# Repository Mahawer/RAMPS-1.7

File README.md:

# RAMPS 1.7

This is an Improvment over the ancient RAMPS 1.4 and later RAMPS 1.5/1.6 made by BIGTREETECH.

Backwards compatible with RAMPS 1.4 in Marlin. All pin definetions are the same.

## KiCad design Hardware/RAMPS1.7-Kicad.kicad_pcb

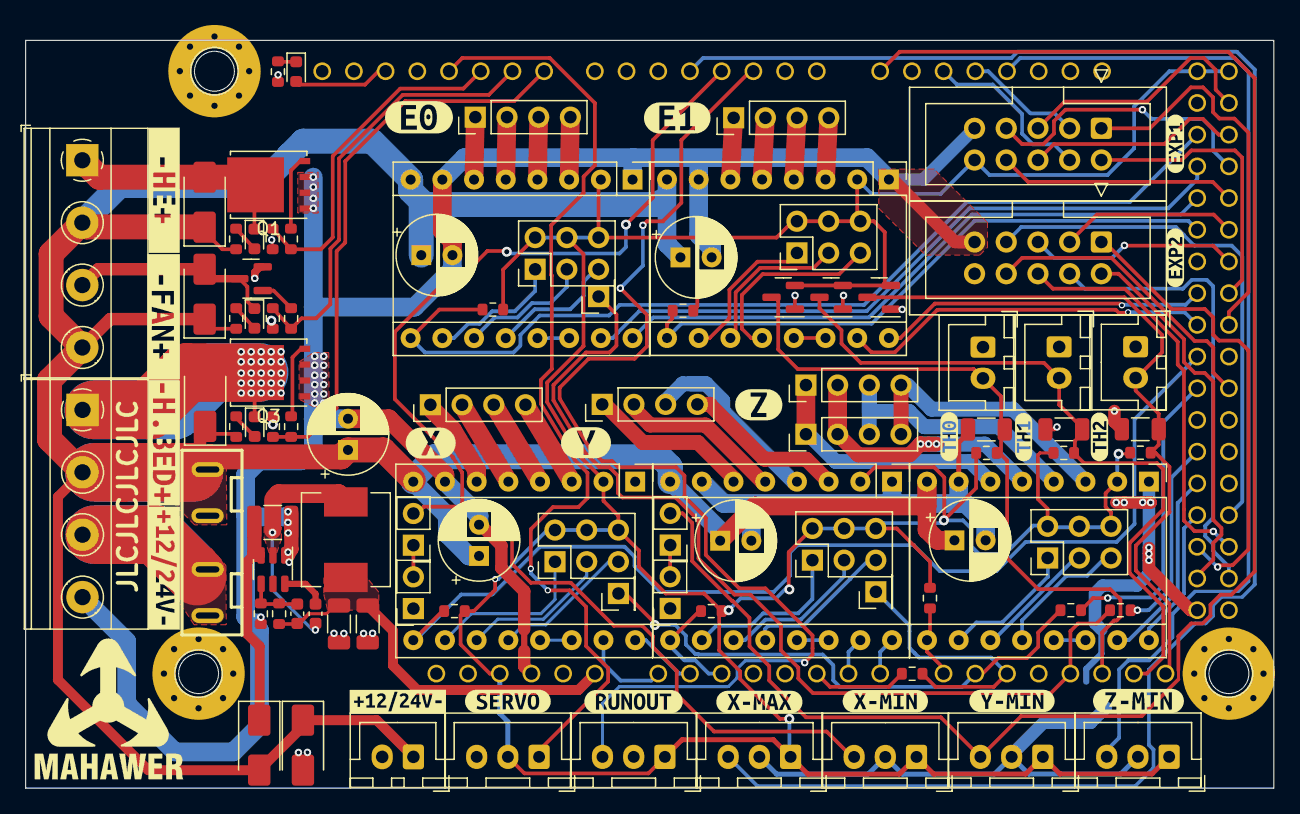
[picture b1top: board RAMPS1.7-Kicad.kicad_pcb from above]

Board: 2 copper layers, 100.0 x 59.9 mm, 117 parts (0 on the bottom side), 111 nets.

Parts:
A1, A2, A3, A4, A5: Pololu_Breakout_A4988; Pololu_Breakout-16_15.2x20.3mm
C1, C2, C3, C4, C5, C14: 100u; CP_Radial_D6.3mm_P2.50mm
C6, C7, C8: 10u; C_1206_3216Metric
C9: 100n; C_0603_1608Metric
C10: 10u; C_1210_3225Metric
C11: 68p; C_0603_1608Metric
C12, C13: 22u; C_1206_3216Metric
D1: LED_Small; LED_0603_1608Metric
D2, D3, D12: BAV99; SOT-23
D4, D5, D6, D8, D10: D; D_SMA
D7, D9, D11: LED; LED_0603_1608Metric
EXP1, EXP2: Conn_02x05_Odd_Even; IDC-Header_2x05_P2.54mm_Vertical
F1: Fuse; FUSE-TH_XF-506P
H1, H2, H3: MountingHole_Pad; MountingHole_3.7mm_Pad_Via
J1, J2: XD; PinSocket_1x02_P2.54mm_Vertical
J3, J4: XS; PinHeader_1x02_P2.54mm_Vertical
J5, J6, J7, J13, J14, J29: X; PinHeader_1x04_P2.54mm_Vertical
J8, J9, J10, J15, J16: Conn_02x03_Odd_Even; PinHeader_2x03_P2.54mm_Vertical
J11, J12, J17: Conn_01x01_Socket; PinHeader_1x01_P2.54mm_Vertical
J18, J30: X-STOP; JST_XH_B3B-XH-A_1x03_P2.50mm_Vertical
J19: Y-STOP; JST_XH_B3B-XH-A_1x03_P2.50mm_Vertical
J20: TH0; JST_XH_B2B-XH-A_1x02_P2.50mm_Vertical
J21: Z-STOP; JST_XH_B3B-XH-A_1x03_P2.50mm_Vertical
J22: TH1; JST_XH_B2B-XH-A_1x02_P2.50mm_Vertical
J23: E0-DET; JST_XH_B3B-XH-A_1x03_P2.50mm_Vertical
J24: E1-DET; JST_XH_B3B-XH-A_1x03_P2.50mm_Vertical
J25: THB; JST_XH_B2B-XH-A_1x02_P2.50mm_Vertical
J26, J28: HEATERS; TerminalBlock_Phoenix_MKDS-1,5-4_1x04_P5.00mm_Horizontal
J27: FAN2; JST_XH_B2B-XH-A_1x02_P2.50mm_Vertical
L1: 10u; L_Sunlord_MWSA0603S
Q1: HY1603; TDSON-8-1
Q2: AO3400A; SOT-23
Q3: HYG023N03; TDSON-8-1
R1, R2, R3, R4, R5: 10K; R_0603_1608Metric
R6, R7, R8, R12, R15, R18, R23: 4.7k; R_0603_1608Metric
R9, R11, R14, R17: 100k; R_0603_1608Metric
R10: 13.3k; R_0603_1608Metric
R13, R16, R19: 10r; R_0603_1608Metric
R20, R21, R22: 1K; R_0603_1608Metric
U1: ARDUINO_MEGA_SHIELD
U2: TPS54202; SOT-23-6
kibuzzard-643BE5C7: G***; kibuzzard-643BE5C7
kibuzzard-643BF197: G***; kibuzzard-643BF197
kibuzzard-643C2A90: G***; kibuzzard-643C2A90
kibuzzard-643C090C: G***; kibuzzard-643C090C
kibuzzard-646BE892: G***; kibuzzard-646BE892
kibuzzard-64628A92: G***; kibuzzard-64628A92
kibuzzard-64628CD2: G***; kibuzzard-64628CD2
kibuzzard-64628D02: G***; kibuzzard-64628D02
kibuzzard-646285C1: G***; kibuzzard-646285C1
kibuzzard-646285F2: G***; kibuzzard-646285F2
kibuzzard-646286CB: G***; kibuzzard-646286CB
kibuzzard-646288A1: G***; kibuzzard-646288A1
kibuzzard-646288B6: G***; kibuzzard-646288B6
kibuzzard-646288C0: G***; kibuzzard-646288C0
kibuzzard-646288CA: G***; kibuzzard-646288CA
kibuzzard-6462874F: G***; kibuzzard-6462874F
kibuzzard-6462890D: G***; kibuzzard-6462890D
kibuzzard-64628626: G***; kibuzzard-64628626
kibuzzard-64628682: G***; kibuzzard-64628682
kibuzzard-64628719: G***; kibuzzard-64628719
kibuzzard-64656097: G***; kibuzzard-64656097

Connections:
+5V: A1.2 (VDD), A2.2 (VDD), A3.2 (VDD), A4.2 (VDD), A5.2 (VDD), D2.2 (A), D3.2 (A), D12.2 (A), EXP1.10, J8.2, J8.4, J8.6, J9.2, J9.4, J9.6, J10.2, J10.4, J10.6, J15.2, J15.4, J15.6, J16.2, J16.4, J16.6, J18.1, J19.1, J21.1, J23.2, J24.1, J30.1, R1.1, R2.1, R3.1, R4.1, R5.1, R6.1, R7.1, R8.1, U1.5V@0, U1.5V@1, U1.5V@2
+24V: A1.8 (VMOT), A2.8 (VMOT), A3.8 (VMOT), A4.8 (VMOT), A5.8 (VMOT), C1.1, C2.1, C3.1, C4.1, C5.1, C14.1, D4.2 (A), D5.1 (K), D6.1 (K), D8.1 (K), D10.1 (K), F1.2, J26.2, J26.4, J27.1, J28.2, R12.2, R15.2, R18.2
A5: R21.2, U1.A5
A9: J11.1, R20.1, U1.A9
A10: J12.1, R21.1, U1.A10
A12: J17.1, R22.1, U1.A12
AM-VIN: C11.1, C12.1, C13.1, L1.2, R9.1, U1.VIN
D4: J24.3, U1.D4
D8: R17.2, R19.2, U1.D8
D9: R14.2, R16.2, U1.D9
D10: R11.2, R13.2, U1.D10
D11: J23.1, U1.D11
D16: EXP1.4, U1.D16
D17: EXP1.3, U1.D17
D23: EXP1.5, U1.D23
D25: EXP1.6, U1.D25
D27: EXP1.7, U1.D27
D29: EXP1.8, U1.D29
D31: EXP2.3, U1.D31
D33: EXP2.5, U1.D33
D35: EXP1.2, U1.D35
D37: EXP1.1, U1.D37
D40: R20.2, U1.D40
D41: EXP2.8, U1.D41
D44: R22.2, U1.D44
D49: EXP2.7, U1.D49
D53: EXP2.4, U1.D53
DCIN: F1.1, J28.3
E0_DIR: A4.16 (DIR), U1.D28
E0_EN: A4.9 (~ENABLE), R4.2, U1.D24
E0_STEP: A4.15 (STEP), U1.D26
E1_DIR: A5.16 (DIR), U1.D34
E1_EN: A5.9 (~ENABLE), R5.2, U1.D30
E1_STEP: A5.15 (STEP), U1.D36
GND: A1.1 (GND), A1.7 (GND), A2.1 (GND), A2.7 (GND), A3.1 (GND), A3.7 (GND), A4.1 (GND), A4.7 (GND), A5.1 (GND), A5.7 (GND), C1.2, C2.2, C3.2, C4.2, C5.2, C6.1, C7.1, C8.1, C10.2, C12.2, C13.2, C14.2, D2.1 (K), D3.1 (K), D5.2 (A), D12.1 (K), EXP1.9, EXP2.9, J18.2, J19.2, J20.1, J21.2, J22.1, J23.3, J24.2, J25.1, J27.2, J28.4, J30.2, Q1.1 (S), Q1.2 (S), Q1.3 (S), Q2.2 (S), Q3.1 (S), Q3.2 (S), Q3.3 (S), R10.2, R11.1, R14.1, R17.1, R23.2, U1.GND@0, U1.GND@1, U1.GND@2, U1.GND@3, U1.GND@4, U2.1 (GND)
LED: D1.2 (A), U1.D13
MISO: EXP2.1, U1.D50
MOSI: EXP2.6, U1.D51
unnamed: A1.4 (1A), J5.3
unnamed: A1.3 (1B), J5.4
unnamed: A1.5 (2A), J5.2
unnamed: A1.6 (2B), J5.1
unnamed: A1.10 (MS1), J8.1
unnamed: A1.11 (MS2), J8.3
unnamed: A1.12 (MS3), J8.5
unnamed: A1.13 (~RESET), A1.14 (~SLEEP)
unnamed: A2.4 (1A), J6.3
unnamed: A2.3 (1B), J6.4
unnamed: A2.5 (2A), J6.2
unnamed: A2.6 (2B), J6.1
unnamed: A2.10 (MS1), J9.1
unnamed: A2.11 (MS2), J9.3
unnamed: A2.12 (MS3), J9.5
unnamed: A2.13 (~RESET), A2.14 (~SLEEP)
unnamed: A3.4 (1A), J7.3, J29.3
unnamed: A3.3 (1B), J7.4, J29.4
unnamed: A3.5 (2A), J7.2, J29.2
unnamed: A3.6 (2B), J7.1, J29.1
unnamed: A3.10 (MS1), J10.1
unnamed: A3.11 (MS2), J10.3
unnamed: A3.12 (MS3), J10.5
unnamed: A3.13 (~RESET), A3.14 (~SLEEP)
unnamed: A4.4 (1A), J13.3
unnamed: A4.3 (1B), J13.4
unnamed: A4.5 (2A), J13.2
unnamed: A4.6 (2B), J13.1
unnamed: A4.10 (MS1), J15.1
unnamed: A4.11 (MS2), J15.3
unnamed: A4.12 (MS3), J15.5
unnamed: A4.13 (~RESET), A4.14 (~SLEEP)
unnamed: A5.4 (1A), J14.3
unnamed: A5.3 (1B), J14.4
unnamed: A5.5 (2A), J14.2
unnamed: A5.6 (2B), J14.1
unnamed: A5.10 (MS1), J16.1
unnamed: A5.11 (MS2), J16.3
unnamed: A5.12 (MS3), J16.5
unnamed: A5.13 (~RESET), A5.14 (~SLEEP)
unnamed: D1.1 (K), R23.1
unnamed: C10.1, D4.1 (K), U2.3 (VIN)
unnamed: D6.2 (A), D7.1 (K), J26.1, Q1.5 (D)
unnamed: D7.2 (A), R12.1
unnamed: D8.2 (A), D9.1 (K), J26.3, Q2.3 (D)
unnamed: D9.2 (A), R15.1
unnamed: D10.2 (A), D11.1 (K), J28.1, Q3.5 (D)
unnamed: D11.2 (A), R18.1
unnamed: J1.2, J3.1
unnamed: J2.2, J4.1
unnamed: Q1.4 (G), R13.1
unnamed: Q2.1 (G), R16.1
unnamed: Q3.4 (G), R19.1
unnamed: C9.1, U2.6 (BOOT)
unnamed: C11.2, R9.2, R10.1, U2.4 (FB)
unnamed: C9.2, L1.1, U2.2 (SW)
SCK: EXP2.2, U1.D52
TH0: C6.2, D2.3 (K), J20.2, R6.2, U1.A13
TH1: C7.2, D3.3 (K), J22.2, R7.2, U1.A14
THB: C8.2, D12.3 (K), J25.2, R8.2, U1.A15
XDG: J3.2, J18.3, U1.D3 (*D3)
X_DIR: A1.16 (DIR), U1.A1
X_EN: A1.9 (~ENABLE), R1.2, U1.D38
X_MAX: J30.3, U1.D2 (*D2)
X_STEP: A1.15 (STEP), U1.A0
YDG: J4.2, J19.3, U1.D14
Y_DIR: A2.16 (DIR), U1.A7
Y_EN: A2.9 (~ENABLE), R2.2, U1.A2
Y_STEP: A2.15 (STEP), U1.A6
Z_DIR: A3.16 (DIR), U1.D48
Z_EN: A3.9 (~ENABLE), R3.2, U1.A8
Z_MIN: J21.3, U1.D18 (*D18)
Z_STEP: A3.15 (STEP), U1.D46

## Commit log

2023-10-18 Update README.md
    Added licensce
